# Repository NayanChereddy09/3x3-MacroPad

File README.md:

# 3x3-MacroPad
The MicroPad is a custom 3x3 macro pad that was designed and built from scratch. It uses Seeed XIAO RP2040 microcontroller and runs QMK firmware to allow full customizability keys. This program allows the user to customized the diffrent keys pressed.
This project includes a custom PCB design, CAD case design, and firmware. The case was designed to hold the PCB securely while keeping the design minimal and clean.
# Why I Made This Project 
I built this project to learn more about hardware design and programming. Specifically, I wanted to practice:

* PCB design using KiCad
* 3D CAD modeling for custom enclosures
* Designing a small keyboard device from scratch

This project helped me understand how hardware, firmware, and mechanical design.
# How to Use the HackPad
+ The macropad will send key presses defined in the QMK firmware keymap.
+ To customize the keys, edit the keymap.c file in the firmware and compile it using QMK.
+ Flash the compiled firmware file (.uf2) to the RP2040 microcontroller.
+ The new keymap will be active after flashing.
# Full CAD Assembly

# PCB Design

# Bill of Materials (BOM)

| Component | Quantity |
|-----------|----------|
| XIAO RP2040 | 1 |
| Switches | 9 |
| Keycaps | 9 |
| Diodes | 9 |
| 0.91" 128x32 OLED Display | 1 |
| M3x16mm Screws | 4 |
| M3x5x4mm Heatset Inserts | 4 |
| PCB (JLCPCB) | 1 |
| 3D Printed Case | 1 |

# Hardware Overview

Microcontroller: Seeed XIAO RP2040

Switches: Cherry MX Switch

Key Layout: 3×3 ortholinear

Firmware: QMK Firmware

Case: Custom designed 3D printed enclosure

# Files Included in This Repository

Firmware - QMK configuration and keymap files

PCB Design - KiCad schematic and PCB layout

CAD Models - 3D enclosure design files and STEP export

BOM - Parts list with purchase links

# Resources
https://blueprint.hackclub.com/hackpad

# License

This project is open-source and available for modification and improvement.

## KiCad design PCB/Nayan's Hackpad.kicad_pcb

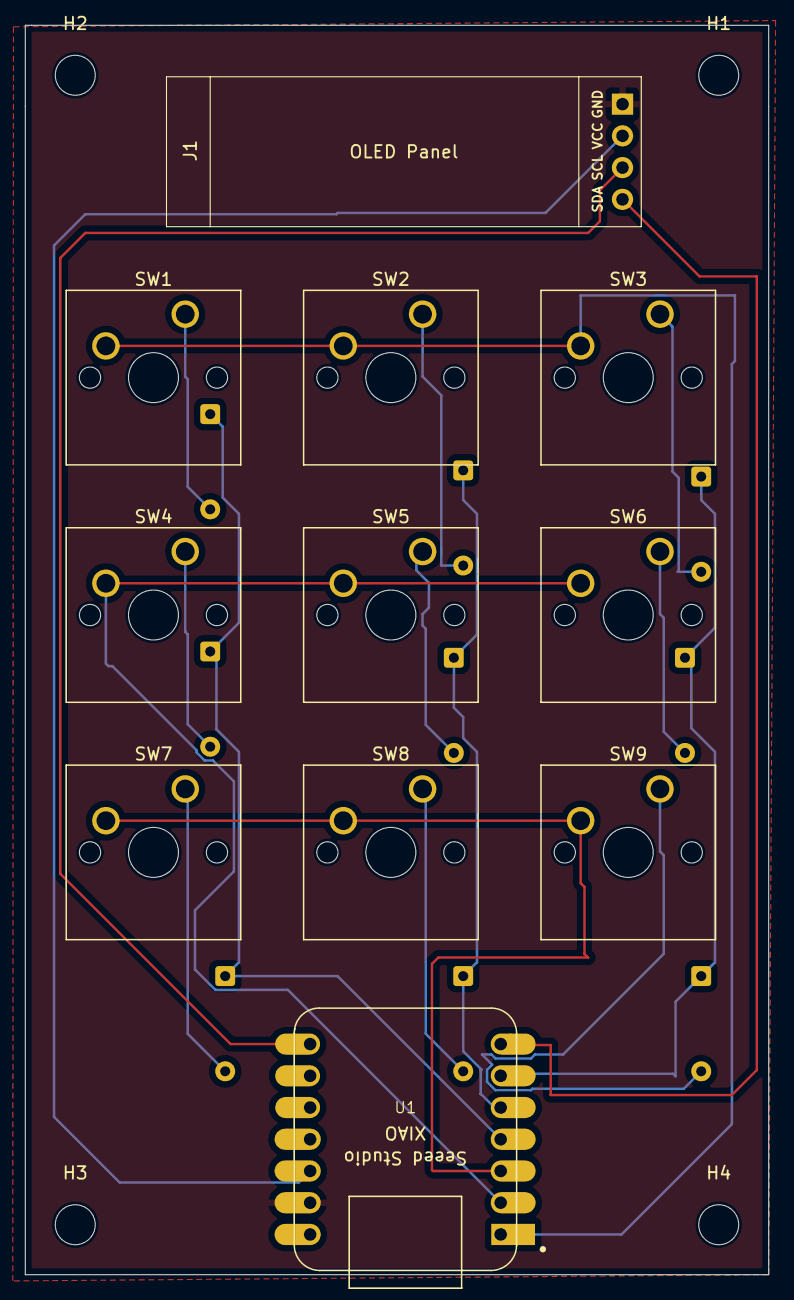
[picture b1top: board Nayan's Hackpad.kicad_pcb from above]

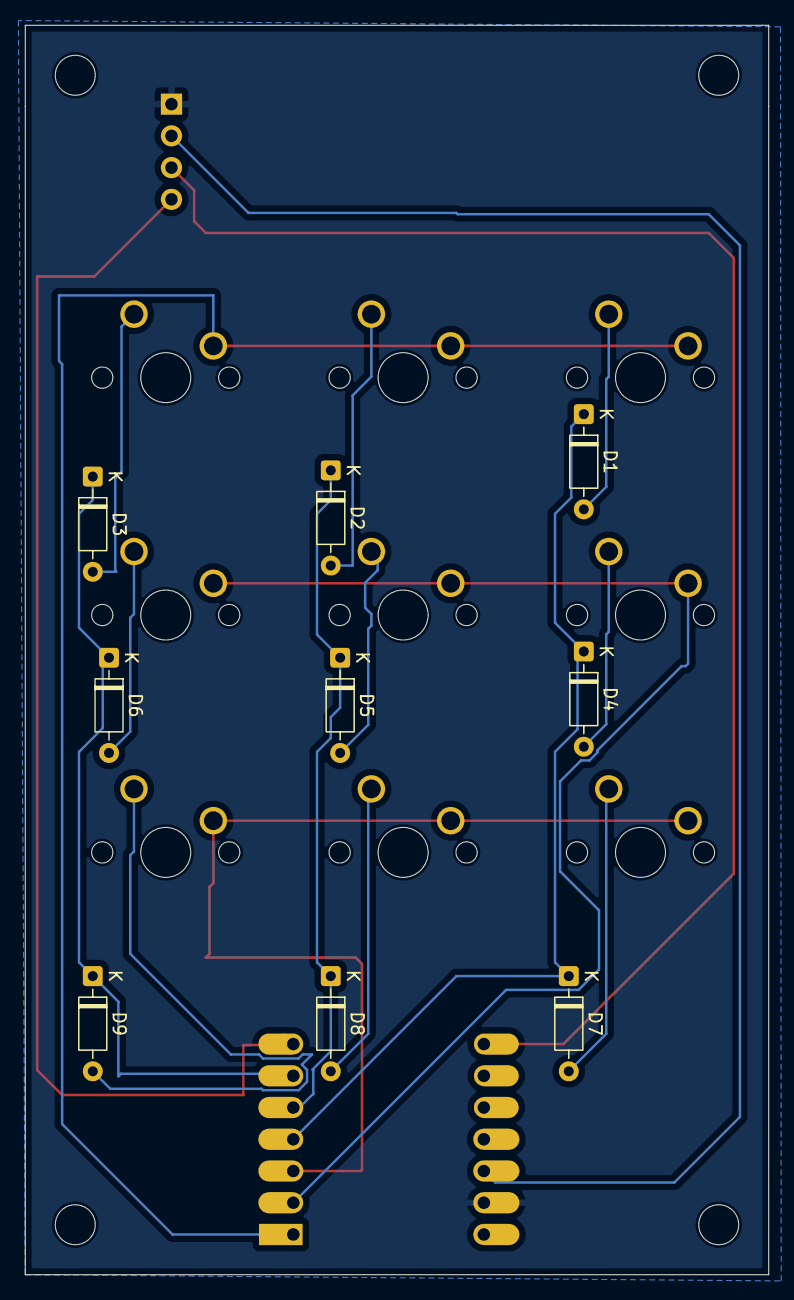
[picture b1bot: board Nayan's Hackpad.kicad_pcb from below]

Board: 2 copper layers, 59.5 x 100.0 mm, 24 parts (9 on the bottom side), 19 nets.

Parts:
D1, D2, D3, D4, D5, D6, D7, D8, D9: 1N4148; D_DO-35_SOD27_P7.62mm_Horizontal
H1, H2, H3, H4: MountingHole; MountingHole_3.2mm_M3
J1: OLED_128x32; SSD1306-0.91-OLED-4pin-128x32
SW1, SW2, SW3, SW4, SW5, SW6, SW7, SW8, SW9: SW_Push; SW_Cherry_MX_1.00u_PCB
U1: MOUDLE-SEEEDUINO-XIAO; XIAO-Generic-Hybrid-14P-2.54-21X17.8MM

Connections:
/SCL: J1.3, U1.8 (PB09_A7_D7_RX)
/SDA: J1.4, U1.7 (PB08_A6_D6_TX)
/VCC: J1.2, U1.12 (3V3)
GND: J1.1, U1.13 (GND)
unnamed: D1.2 (A), SW1.1
unnamed: D1.1 (K), D4.1 (K), D7.1 (K), U1.4 (PA11_A3_D3)
unnamed: D2.2 (A), SW2.1
unnamed: D2.1 (K), D5.1 (K), D8.1 (K), U1.5 (PA8_A4_D4_SDA)
unnamed: D3.2 (A), SW3.1
unnamed: D3.1 (K), D6.1 (K), D9.1 (K), U1.6 (PA9_A5_D5_SCL)
unnamed: D4.2 (A), SW4.1
unnamed: D5.2 (A), SW5.1
unnamed: D6.2 (A), SW6.1
unnamed: D7.2 (A), SW7.1
unnamed: D8.2 (A), SW8.1
unnamed: D9.2 (A), SW9.1
unnamed: SW1.2, SW2.2, SW3.2, U1.1 (PA02_A0_D0)
unnamed: SW4.2, SW5.2, SW6.2, U1.2 (PA4_A1_D1)
unnamed: SW7.2, SW8.2, SW9.2, U1.3 (PA10_A2_D2)

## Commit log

2026-03-13 Revise BOM with pricing and new components
    Updated the Bill of Materials (BOM) to include prices and additional components.
2026-03-13 Add files via upload
    CAD files
2026-03-13 Add files via upload
    PCB
2026-03-13 Add files via upload
    GBR file
2026-03-13 Add files via upload
    Software QMK
2026-03-13 Add files via upload
    journal
2026-03-13 Add files via upload
    Nayan's Hackpad With PCB
2026-03-13 Fix total calculations in README.md
    Corrected total calculations in the README.
2026-03-13 Add files via upload
    BOM
2026-03-13 Add currency to total cost in README
    Updated total cost lines to include currency (CAD).
2026-03-13 Add Resources section with Hack Club link
2026-03-13 Revise PCB and 3D printed case pricing in README
    Updated prices and links for PCB and 3D printed case.
2026-03-13 Modify component details in Macro BOM
    Updated prices and links for various components in the BOM.
2026-03-16 Revise BOM with updated prices and links
    Updated the Bill of Materials (BOM) with new pricing and links.
2026-03-16 Refactor Final BOM.csv to remove price and link
    Removed price and link columns from the BOM.
2026-03-16 Revise BOM format and remove pricing details
    Updated the Bill of Materials (BOM) section to remove price details and added a subtotal, tax, and total cost.
2026-03-16 Add PCB design screenshots to README
    Added additional PCB design screenshots to the README.
2026-03-16 Added files
2026-03-17 Clarify project description in README.md
    Removed the phrase 'without using a faceplate' for clarity.
2026-03-17 Top plate
